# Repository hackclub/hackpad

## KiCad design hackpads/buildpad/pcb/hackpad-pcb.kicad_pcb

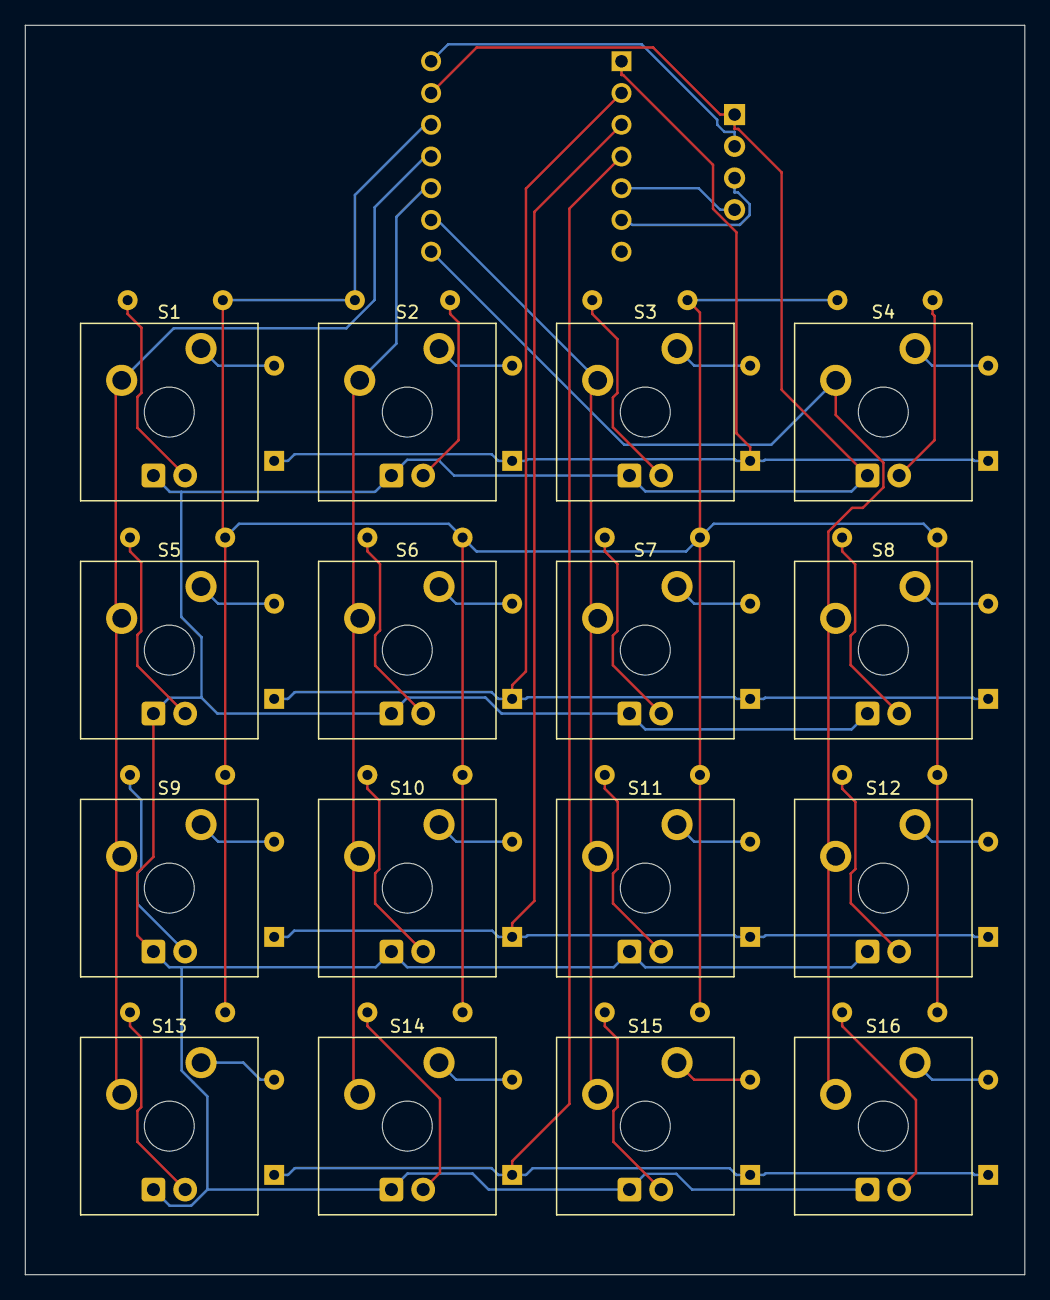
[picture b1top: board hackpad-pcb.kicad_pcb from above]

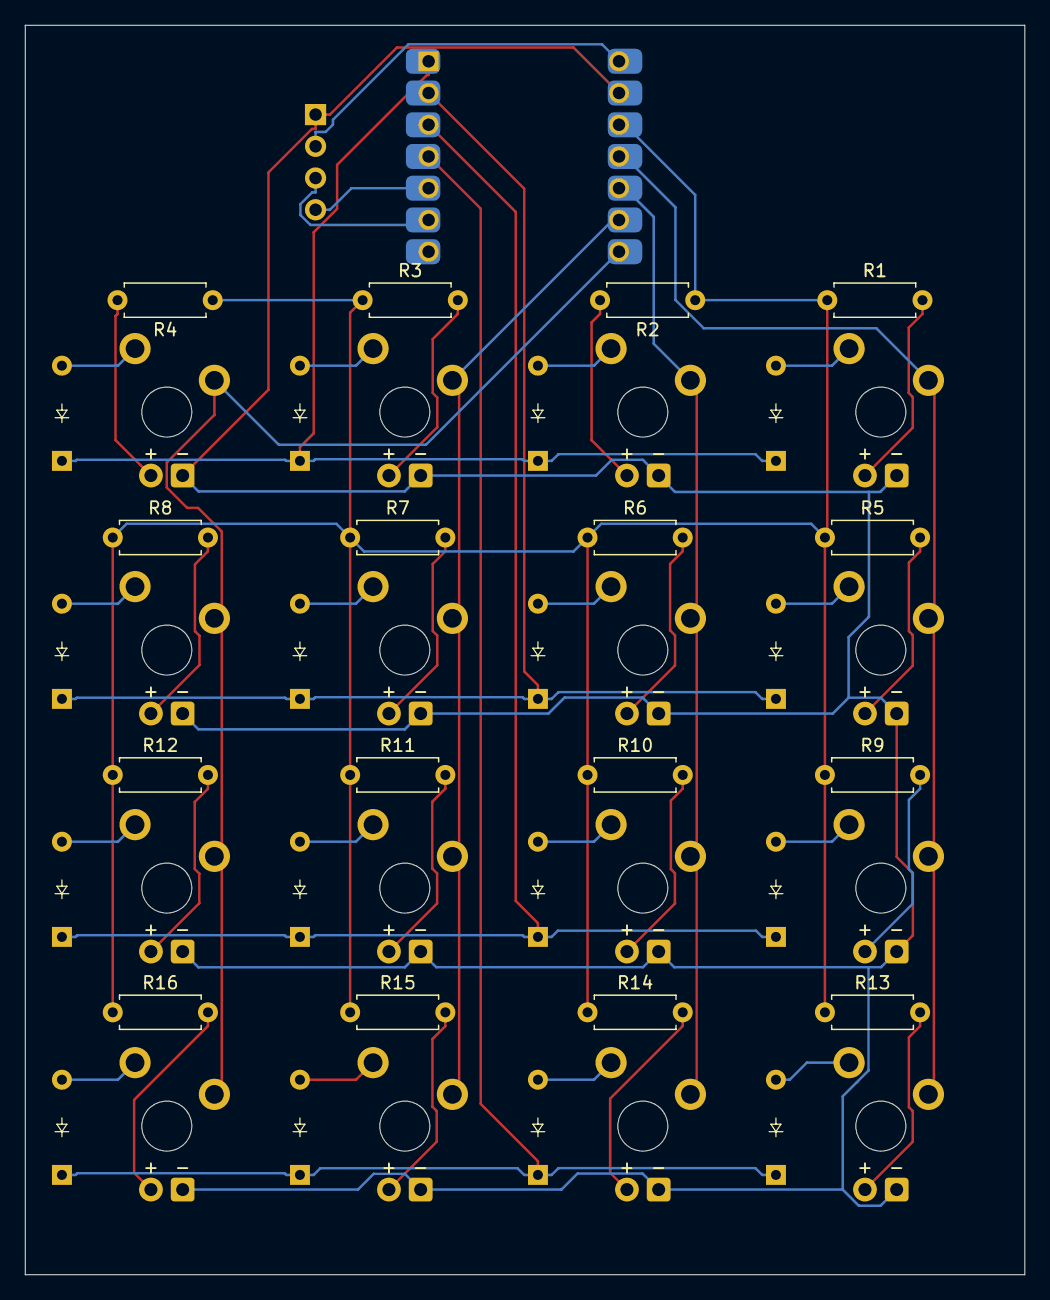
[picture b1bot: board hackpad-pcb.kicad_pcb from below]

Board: 2 copper layers, 80.0 x 100.0 mm, 66 parts (33 on the bottom side), 45 nets.

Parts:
D1, D2, D3, D4, D5, D6, D7, D8, D9, D10, D11, D12, D13, D14, D15, D16: Diode; Diode_DO-35
D17, D18, D19, D20, D21, D22, D23, D24, D25, D26, D27, D28, D29, D30, D31, D32: LED; LED_MX_3mm-ROT
J1: OLED_128x32
R1, R2, R3, R4, R5, R6, R7, R8, R9, R10, R11, R12, R13, R14, R15, R16: R; R_Axial_DIN0207_L6.3mm_D2.5mm_P7.62mm_Horizontal
S1, S2, S3, S4, S5, S6, S7, S8, S9, S10, S11, S12, S13, S14, S15, S16: Keyswitch; MX_Plate_1.00u
U1: MCU_Seeed_XIAO_RP2040; Seeed_XIAO_RP2040

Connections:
+3V3: R1.1, R2.1, R3.1, R4.1, R5.1, R6.1, R7.1, R8.1, R9.1, R10.1, R11.1, R12.1, R13.1, R14.1, R15.1, R16.1, U1.12 (3V3)
Column 0: S1.1, S5.1, S9.1, S13.1, U1.11 (PA6_A10_D10_MOSI)
Column 1: S2.1, S6.1, S10.1, S14.1, U1.10 (PA5_A9_D9_MISO)
Column 2: S3.1, S7.1, S11.1, S15.1, U1.9 (PA7_A8_D8_SCK)
Column 3: S4.1, S8.1, S12.1, S16.1, U1.8 (PB09_A7_D7_RX)
GND: D17.1 (K), D18.1 (K), D19.1 (K), D20.1 (K), D21.1 (K), D22.1 (K), D23.1 (K), D24.1 (K), D25.1 (K), D26.1 (K), D27.1 (K), D28.1 (K), D29.1 (K), D30.1 (K), D31.1 (K), D32.1 (K), J1.1 (GND), U1.13 (GND)
unnamed: D1.2 (A), S1.2
unnamed: D2.2 (A), S2.2
unnamed: D3.2 (A), S3.2
unnamed: D4.2 (A), S4.2
unnamed: D5.2 (A), S5.2
unnamed: D6.2 (A), S6.2
unnamed: D7.2 (A), S7.2
unnamed: D8.2 (A), S8.2
unnamed: D9.2 (A), S9.2
unnamed: D10.2 (A), S10.2
unnamed: D11.2 (A), S11.2
unnamed: D12.2 (A), S12.2
unnamed: D13.2 (A), S13.2
unnamed: D14.2 (A), S14.2
unnamed: D15.2 (A), S15.2
unnamed: D16.2 (A), S16.2
unnamed: D17.2 (A), R1.2
unnamed: D18.2 (A), R2.2
unnamed: D19.2 (A), R3.2
unnamed: D20.2 (A), R4.2
unnamed: D21.2 (A), R5.2
unnamed: D22.2 (A), R6.2
unnamed: D23.2 (A), R7.2
unnamed: D24.2 (A), R8.2
unnamed: D25.2 (A), R9.2
unnamed: D26.2 (A), R10.2
unnamed: D27.2 (A), R11.2
unnamed: D28.2 (A), R12.2
unnamed: D29.2 (A), R13.2
unnamed: D30.2 (A), R14.2
unnamed: D31.2 (A), R15.2
unnamed: D32.2 (A), R16.2
Row 0: D1.1 (K), D2.1 (K), D3.1 (K), D4.1 (K), U1.1 (PA02_A0_D0)
Row 1: D5.1 (K), D6.1 (K), D7.1 (K), D8.1 (K), U1.2 (PA4_A1_D1)
Row 2: D9.1 (K), D10.1 (K), D11.1 (K), D12.1 (K), U1.3 (PA10_A2_D2)
Row 3: D13.1 (K), D14.1 (K), D15.1 (K), D16.1 (K), U1.4 (PA11_A3_D3)
SCL: J1.3 (SCL), U1.6 (PA9_A5_D5_SCL)
SDA: J1.4 (SDA), U1.5 (PA8_A4_D4_SDA)
VCC: J1.2 (VCC), U1.14 (5V)

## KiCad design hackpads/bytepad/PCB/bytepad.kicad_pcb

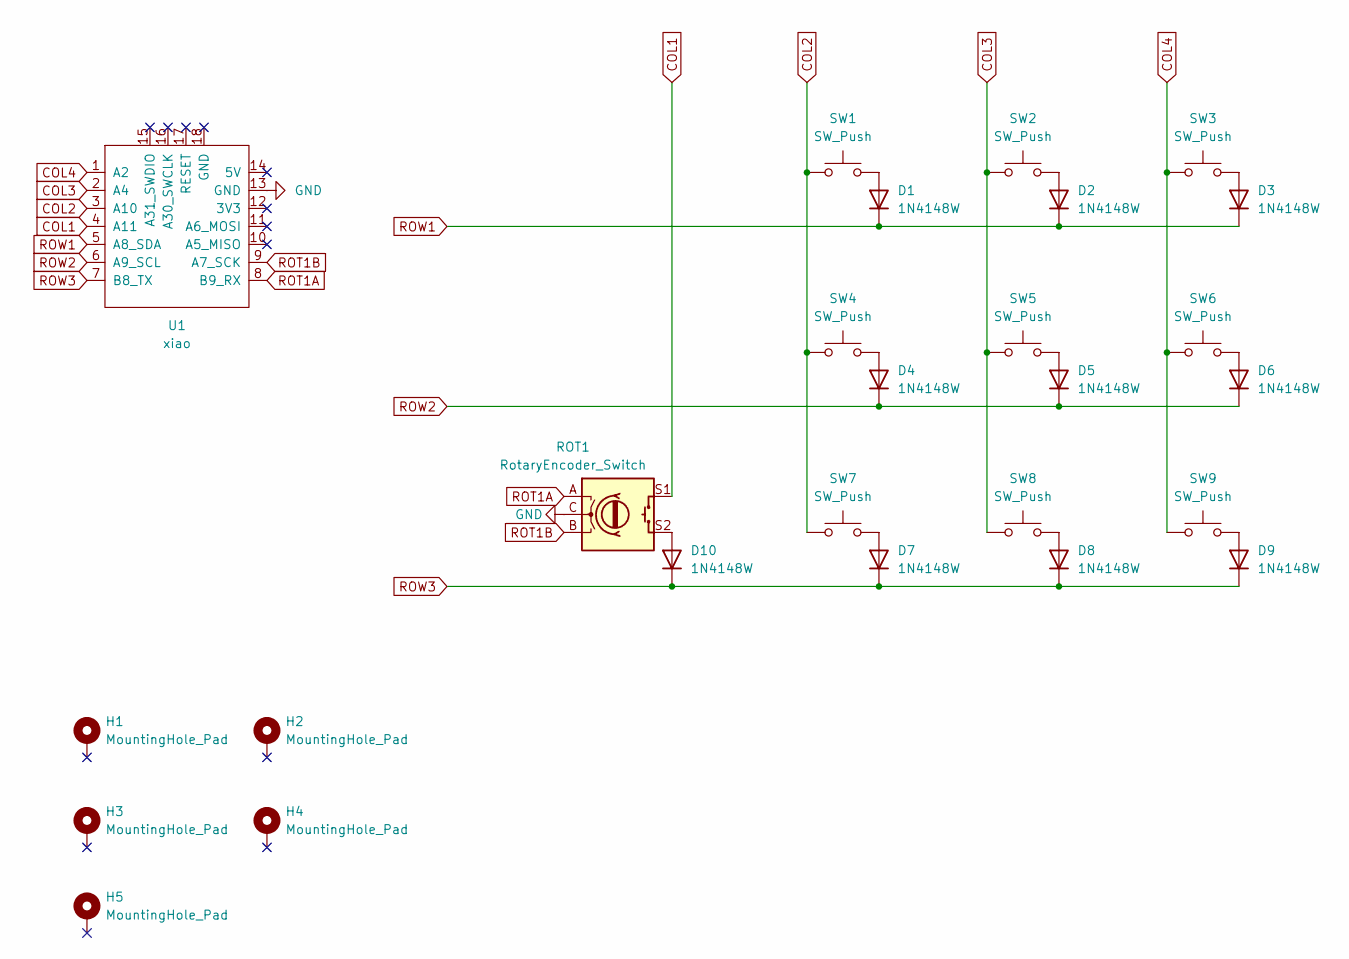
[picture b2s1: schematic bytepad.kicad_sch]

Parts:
D1, D2, D3, D4, D5, D6, D7, D8, D9, D10: 1N4148W; D_SOD-123
H1, H2, H3, H4, H5: MountingHole_Pad; MountingHole_2.2mm_M2_DIN965_Pad
ROT1: RotaryEncoder_Switch; RotaryEncoder_EC11
SW1, SW2, SW3, SW4, SW5, SW6, SW7, SW8, SW9: SW_Push; pg1350-H
U1: xiao; xiao-tht

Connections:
COL1: ROT1.S1, U1.4 (A11)
COL2: SW1.1, SW4.1, SW7.1, U1.3 (A10)
COL3: SW2.1, SW5.1, SW8.1, U1.2 (A4)
COL4: SW3.1, SW6.1, SW9.1, U1.1 (A2)
GND: ROT1.C, U1.13 (GND)
unnamed: D1.2 (A), SW1.2
unnamed: D2.2 (A), SW2.2
unnamed: D3.2 (A), SW3.2
unnamed: D4.2 (A), SW4.2
unnamed: D5.2 (A), SW5.2
unnamed: D6.2 (A), SW6.2
unnamed: D7.2 (A), SW7.2
unnamed: D8.2 (A), SW8.2
unnamed: D9.2 (A), SW9.2
unnamed: D10.2 (A), ROT1.S2
ROT1A: ROT1.A, U1.8 (B9_RX)
ROT1B: ROT1.B, U1.9 (A7_SCK)
ROW1: D1.1 (K), D2.1 (K), D3.1 (K), U1.5 (A8_SDA)
ROW2: D4.1 (K), D5.1 (K), D6.1 (K), U1.6 (A9_SCL)
ROW3: D7.1 (K), D8.1 (K), D9.1 (K), D10.1 (K), U1.7 (B8_TX)

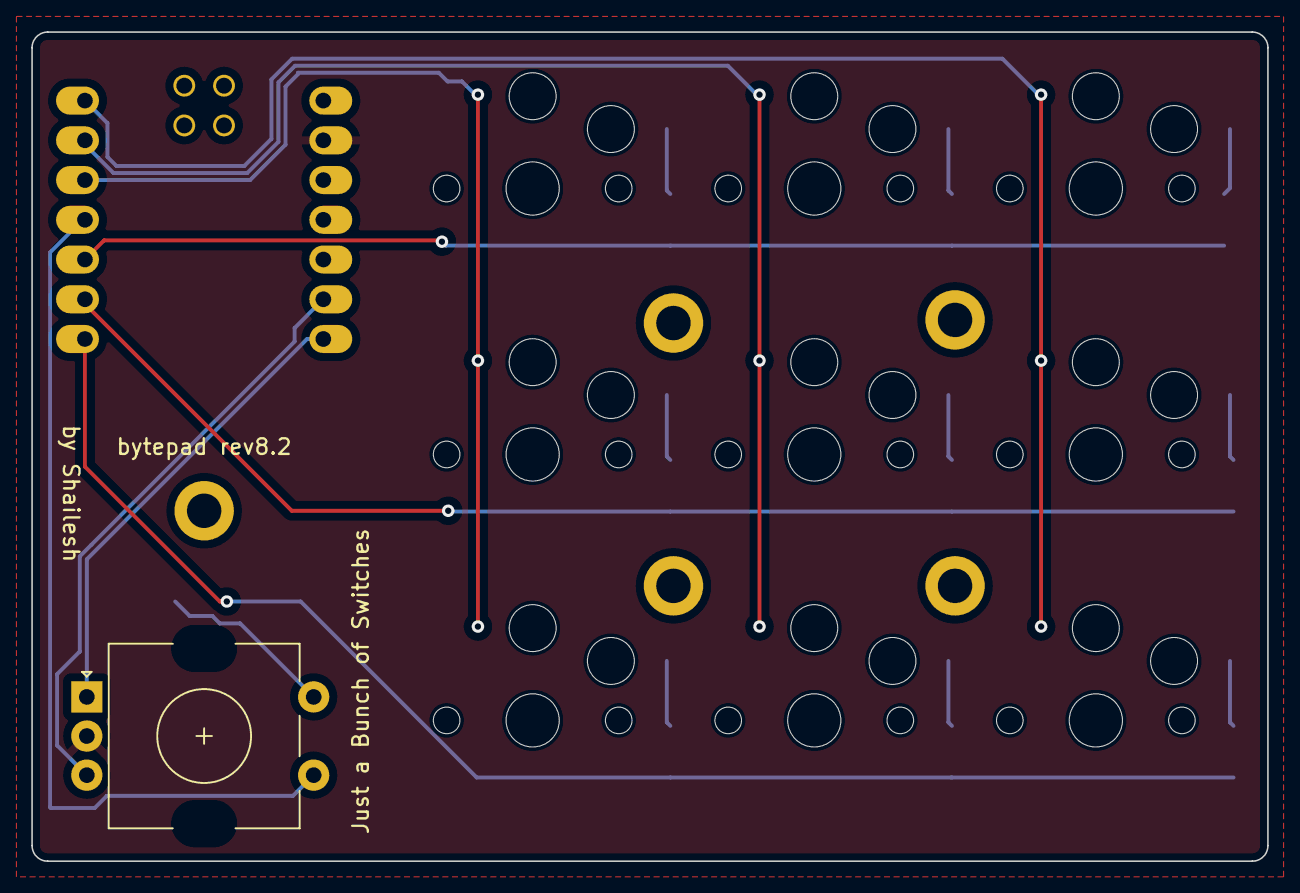
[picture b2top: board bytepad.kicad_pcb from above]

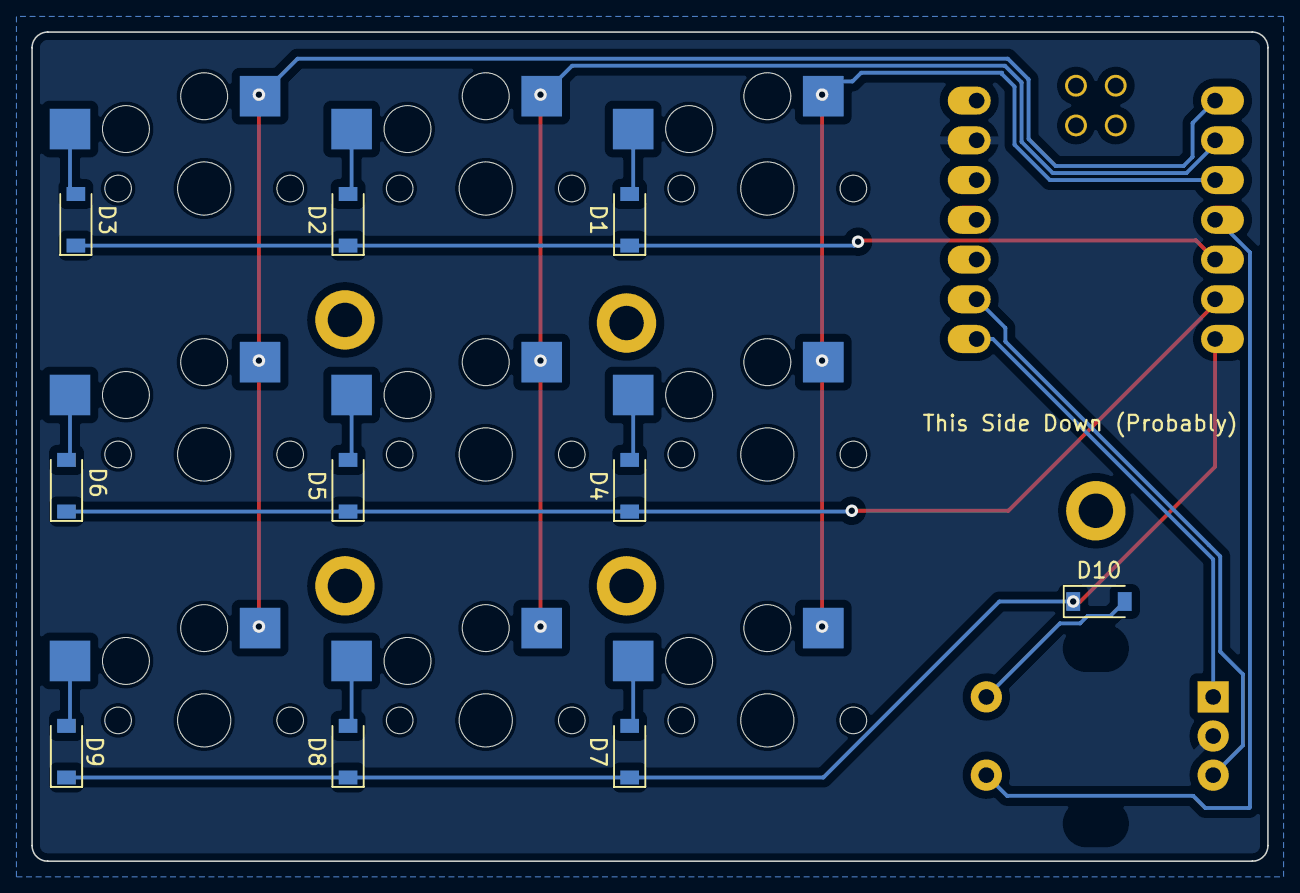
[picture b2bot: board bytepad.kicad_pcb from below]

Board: 2 copper layers, 79.0 x 53.0 mm, 26 parts (10 on the bottom side), 20 nets.

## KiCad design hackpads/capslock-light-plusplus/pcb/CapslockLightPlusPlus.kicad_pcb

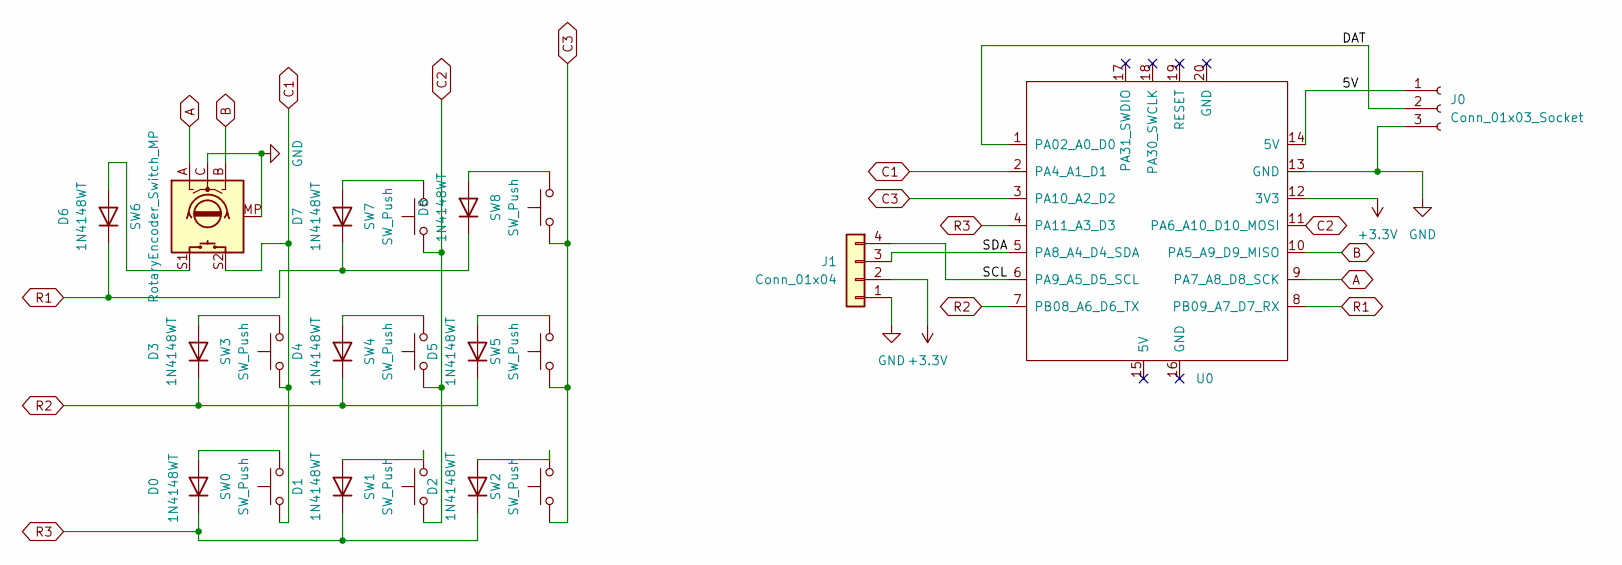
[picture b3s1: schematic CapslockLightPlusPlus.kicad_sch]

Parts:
D0, D1, D2, D3, D4, D5, D6, D7, D8: 1N4148WT; DIODE-1N4148
J0: Conn_01x03_Socket; SolderJumper-3_P1.3mm_Open_Pad1.0x1.5mm
J1: Conn_01x04; SSD1306-0.91-OLED-4pin-128x32
SW0, SW1, SW2, SW3, SW4, SW5, SW7, SW8: SW_Push; SW_Cherry_MX_1.00u_PCB
SW6: RotaryEncoder_Switch_MP; RotaryEncoder_Alps_EC12E-Switch_Vertical_H20mm
U0: Seeed Studio XIAO SAMD21; XIAO-Generic-Hybrid-14P-2.54-21X17.8MM

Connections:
+3.3V: J1.2 (Pin_3), U0.12 (3V3)
/5V: J0.1, U0.14 (5V)
/DAT: J0.2, U0.1 (PA02_A0_D0)
/SCL: J1.4 (Pin_1), U0.6 (PA9_A5_D5_SCL)
/SDA: J1.3 (Pin_2), U0.5 (PA8_A4_D4_SDA)
A: SW6.A, U0.9 (PA7_A8_D8_SCK)
B: SW6.B, U0.10 (PA5_A9_D9_MISO)
C1: SW0.1, SW3.1, SW6.S2, U0.2 (PA4_A1_D1)
C2: SW1.1, SW4.1, SW7.1, U0.11 (PA6_A10_D10_MOSI)
C3: SW2.1, SW5.1, SW8.1, U0.3 (PA10_A2_D2)
GND: J0.3, J1.1 (Pin_4), SW6.C, SW6.MP, U0.13 (GND)
unnamed: D0.2 (A), SW0.2
unnamed: D1.2 (A), SW1.2
unnamed: D2.2 (A), SW2.2
unnamed: D3.2 (A), SW3.2
unnamed: D4.2 (A), SW4.2
unnamed: D5.2 (A), SW5.2
unnamed: D6.2 (A), SW6.S1
unnamed: D7.2 (A), SW7.2
unnamed: D8.2 (A), SW8.2
R1: D6.1 (K), D7.1 (K), D8.1 (K), U0.8 (PB09_A7_D7_RX)
R2: D3.1 (K), D4.1 (K), D5.1 (K), U0.7 (PB08_A6_D6_TX)
R3: D0.1 (K), D1.1 (K), D2.1 (K), U0.4 (PA11_A3_D3)

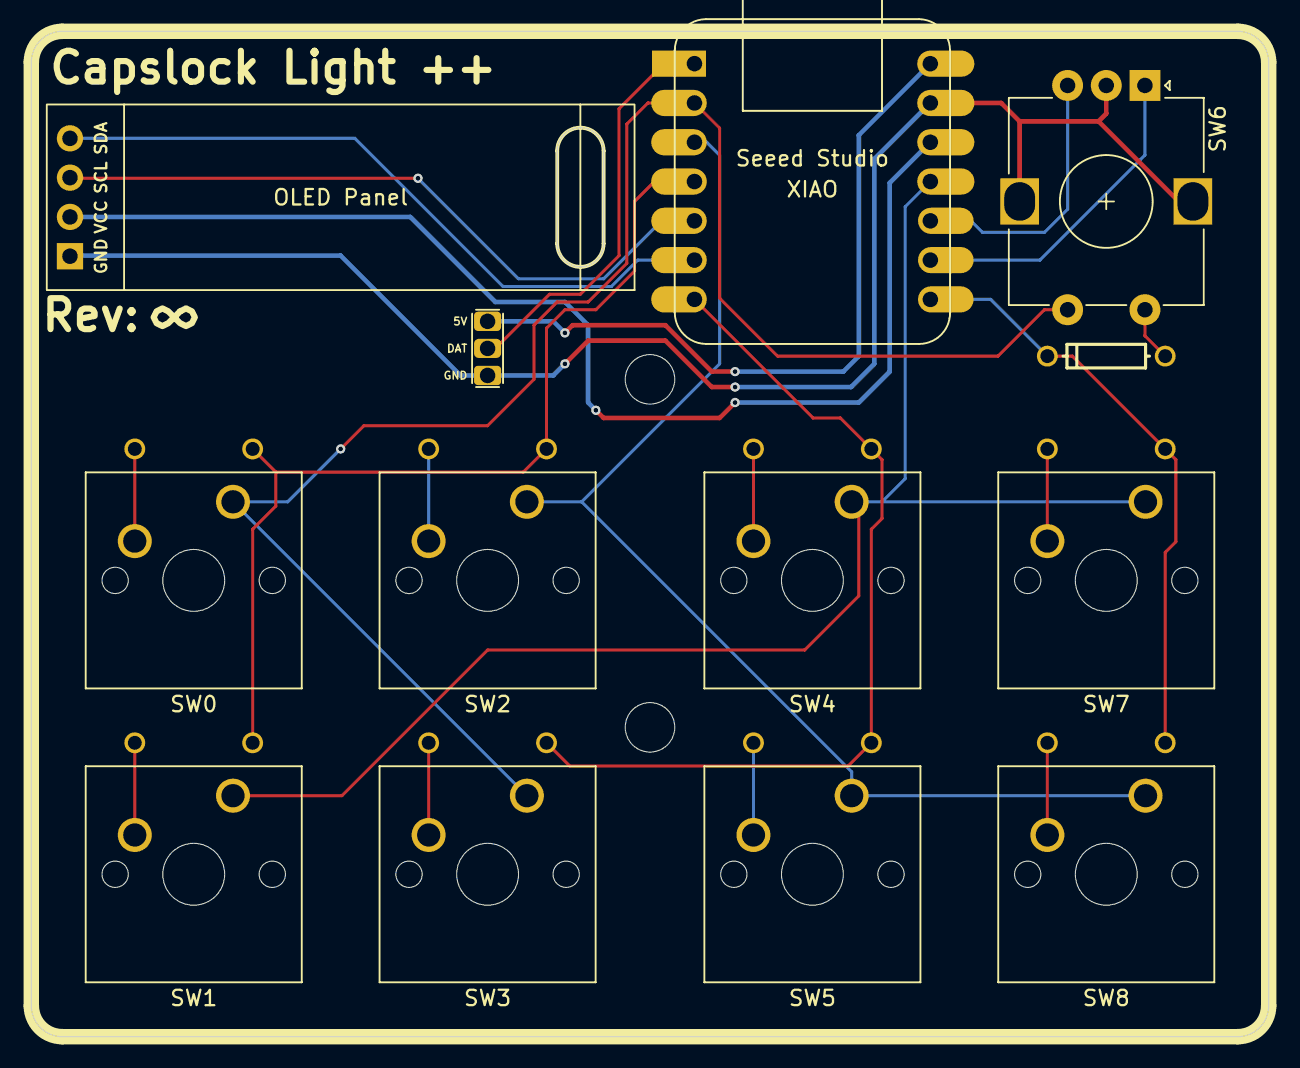
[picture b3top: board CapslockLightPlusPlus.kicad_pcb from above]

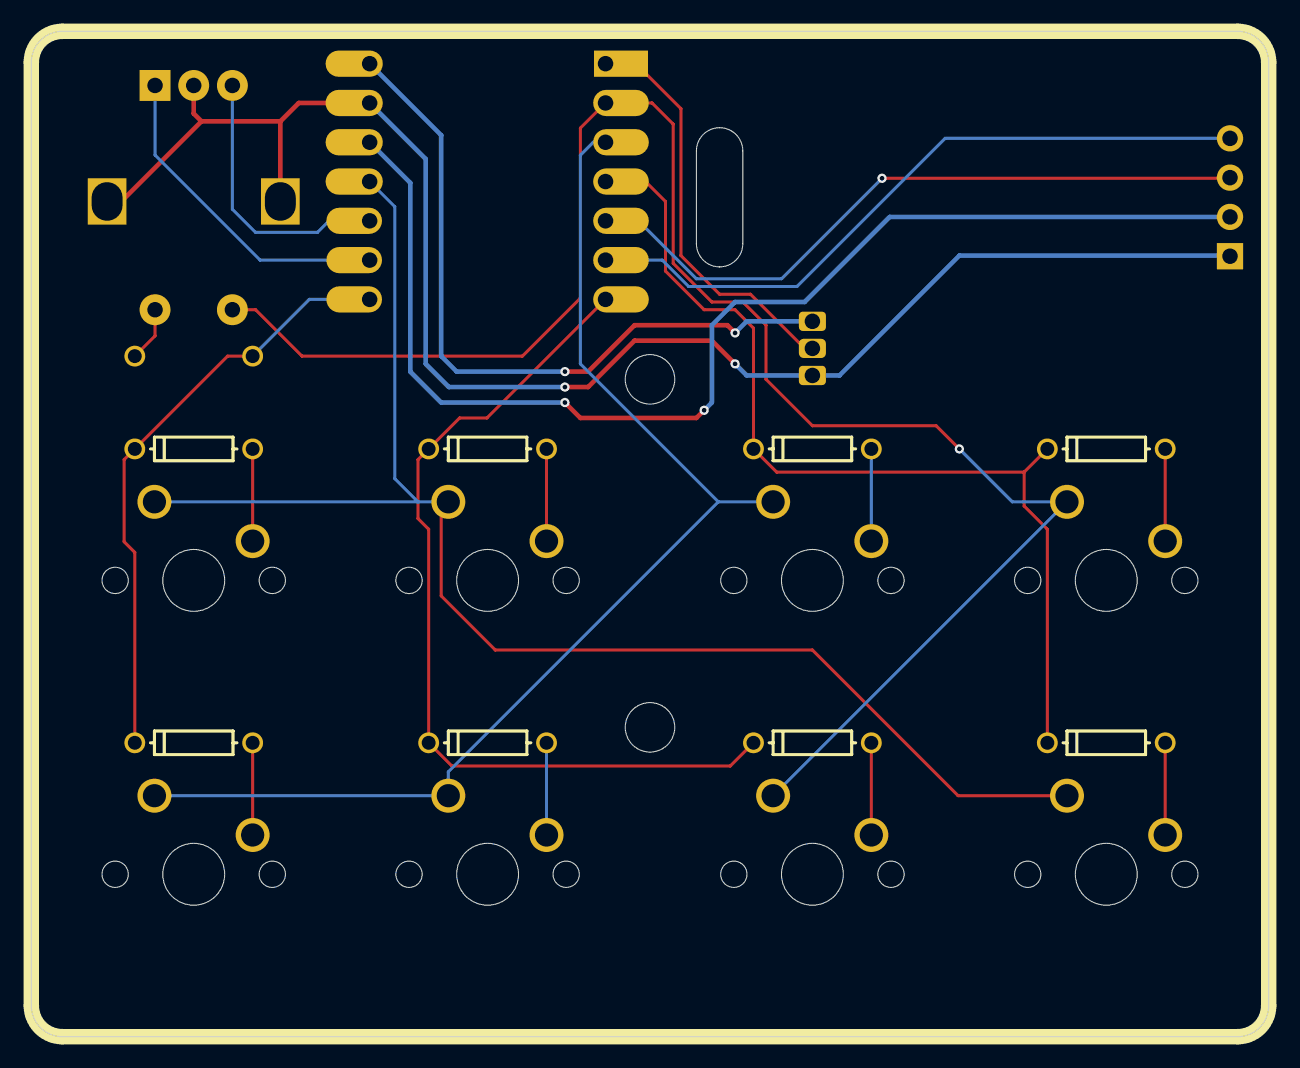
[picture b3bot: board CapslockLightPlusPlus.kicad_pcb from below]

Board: 2 copper layers, 80.0 x 65.0 mm, 21 parts (8 on the bottom side), 23 nets.

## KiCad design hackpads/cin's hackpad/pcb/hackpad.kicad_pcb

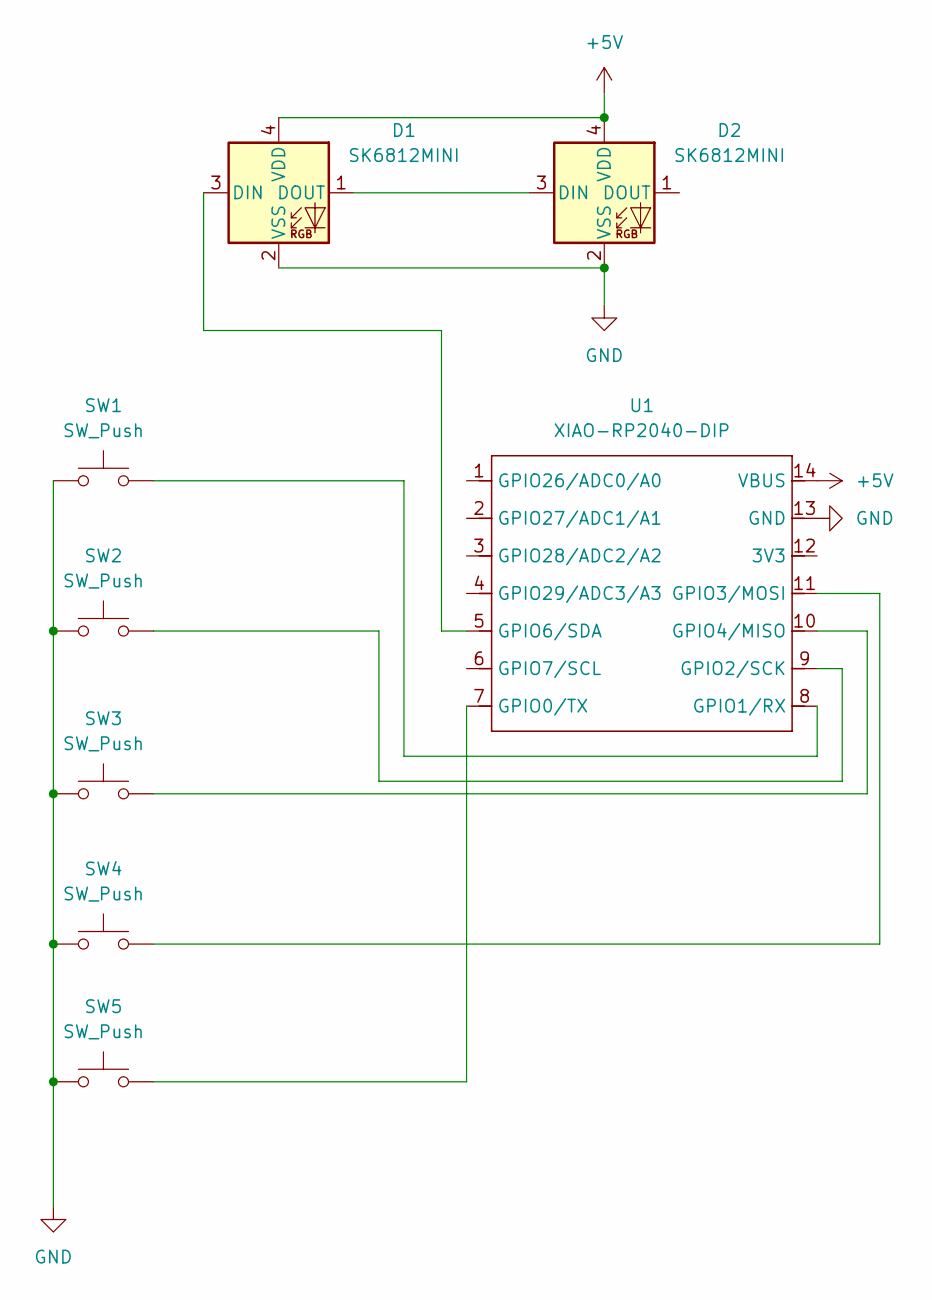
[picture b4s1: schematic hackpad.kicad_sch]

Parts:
D1, D2: SK6812MINI; LED_SK6812MINI_PLCC4_3.5x3.5mm_P1.75mm
SW1, SW2, SW3, SW4, SW5: SW_Push; SW_Cherry_MX_1.00u_PCB
U1: XIAO-RP2040-DIP

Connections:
+5V: D1.4 (VDD), D2.4 (VDD), U1.14 (VBUS)
GND: D1.2 (VSS), D2.2 (VSS), SW1.1, SW2.1, SW3.1, SW4.1, SW5.1, U1.13 (GND)
unnamed: D1.3 (DIN), U1.5 (GPIO6/SDA)
unnamed: D1.1 (DOUT), D2.3 (DIN)
unnamed: SW5.2, U1.7 (GPIO0/TX)
unnamed: SW1.2, U1.8 (GPIO1/RX)
unnamed: SW2.2, U1.9 (GPIO2/SCK)
unnamed: SW4.2, U1.11 (GPIO3/MOSI)
unnamed: SW3.2, U1.10 (GPIO4/MISO)

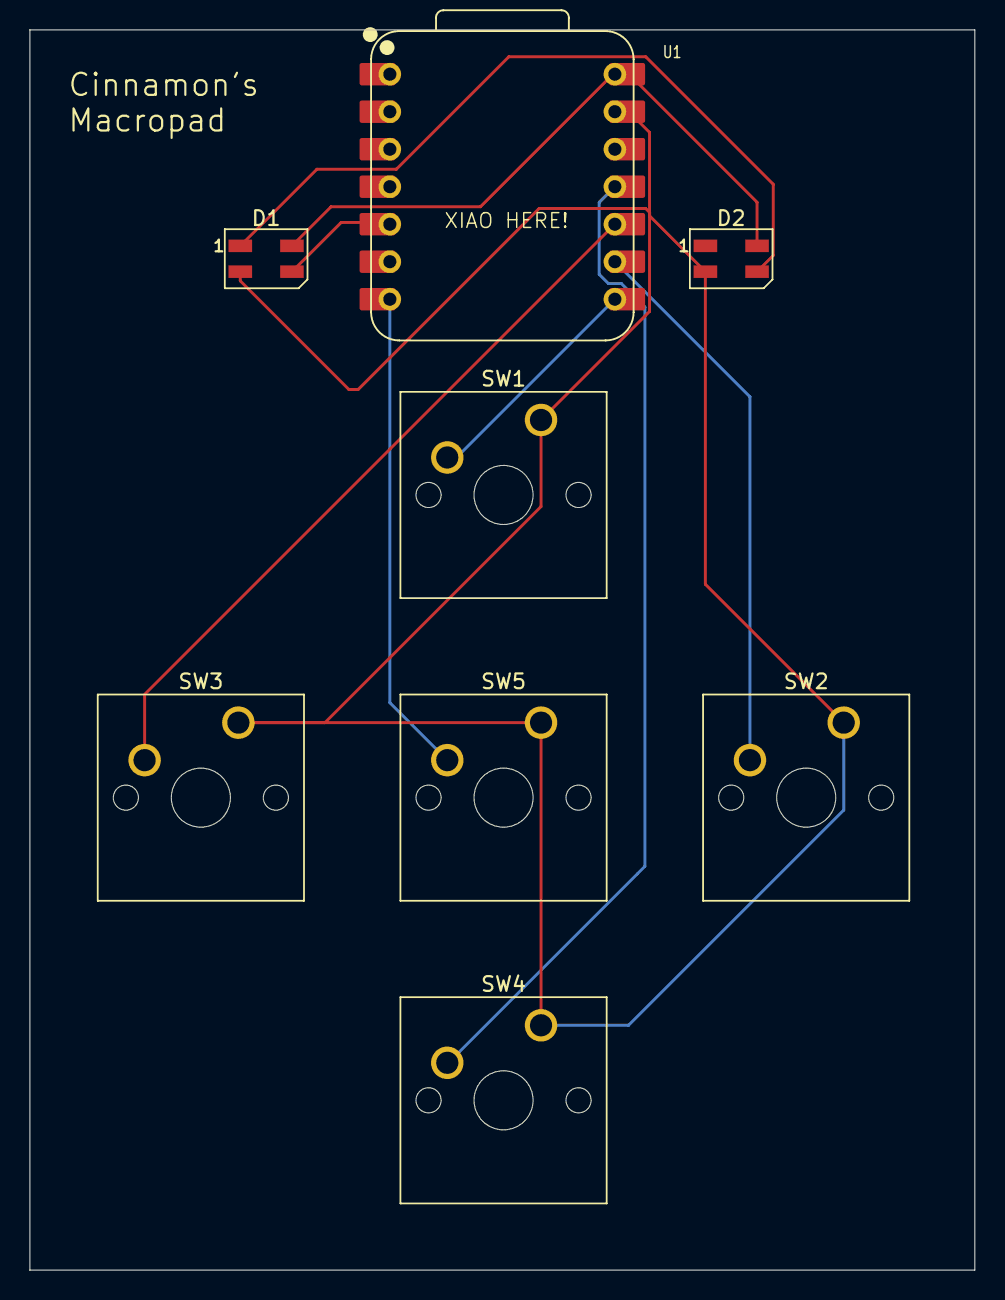
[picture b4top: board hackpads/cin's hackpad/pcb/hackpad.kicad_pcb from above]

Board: 2 copper layers, 64.0 x 84.0 mm, 8 parts (0 on the bottom side), 9 nets.

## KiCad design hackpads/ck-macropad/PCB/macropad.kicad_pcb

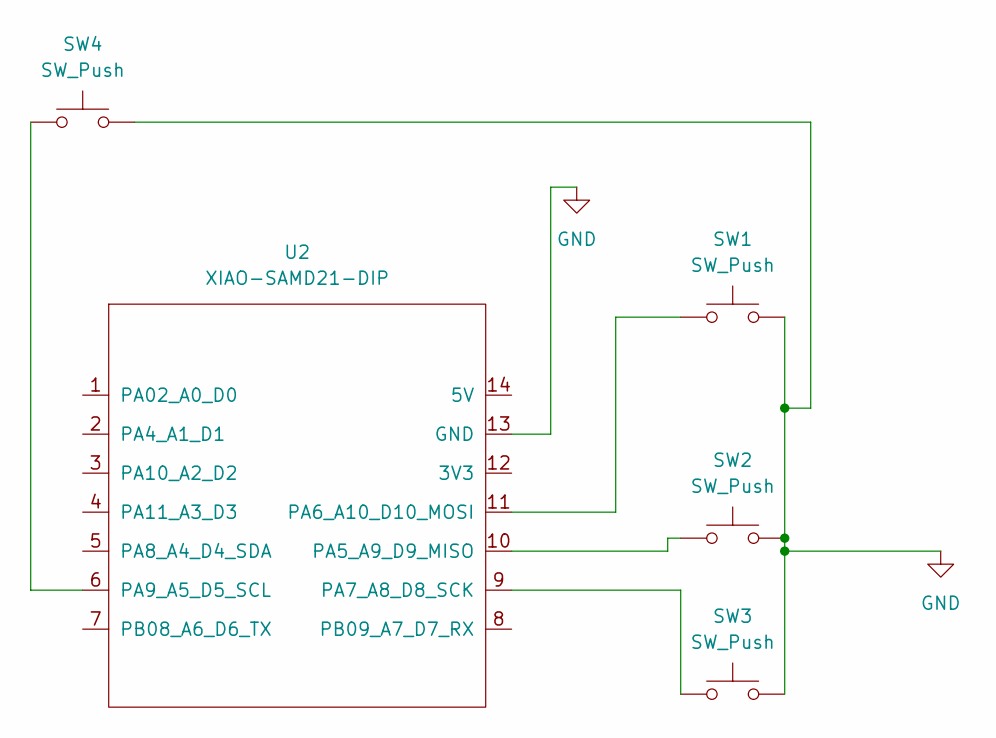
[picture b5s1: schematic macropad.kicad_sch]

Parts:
SW1, SW2, SW3, SW4: SW_Push; SW_Cherry_MX_1.00u_PCB
U2: XIAO-SAMD21-DIP; XIAO-nRF52840-DIP

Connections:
GND: SW1.2, SW2.2, SW3.2, SW4.2, U2.13 (GND)
unnamed: SW2.1, U2.10 (PA5_A9_D9_MISO)
unnamed: SW1.1, U2.11 (PA6_A10_D10_MOSI)
unnamed: SW3.1, U2.9 (PA7_A8_D8_SCK)
unnamed: SW4.1, U2.6 (PA9_A5_D5_SCL)

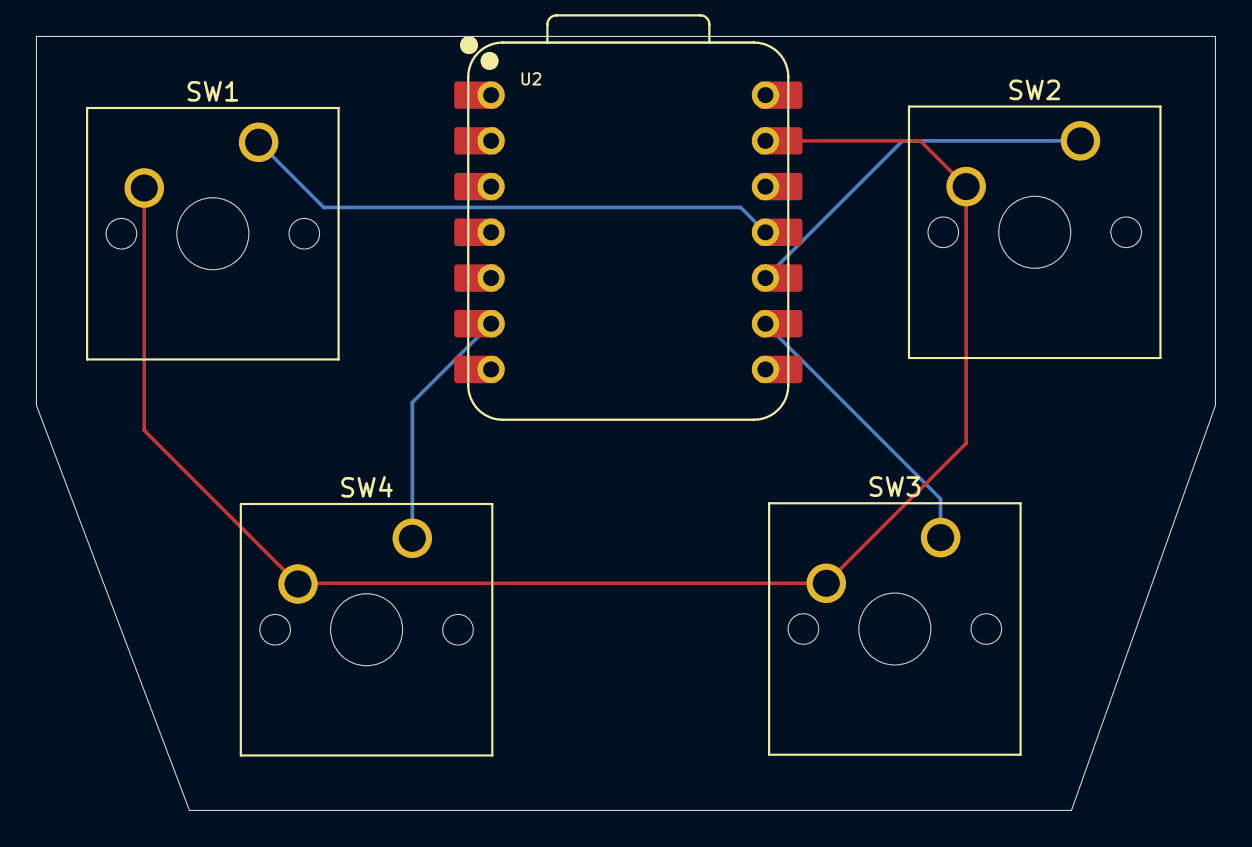
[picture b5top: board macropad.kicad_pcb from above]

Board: 2 copper layers, 65.5 x 43.0 mm, 5 parts (0 on the bottom side), 5 nets.

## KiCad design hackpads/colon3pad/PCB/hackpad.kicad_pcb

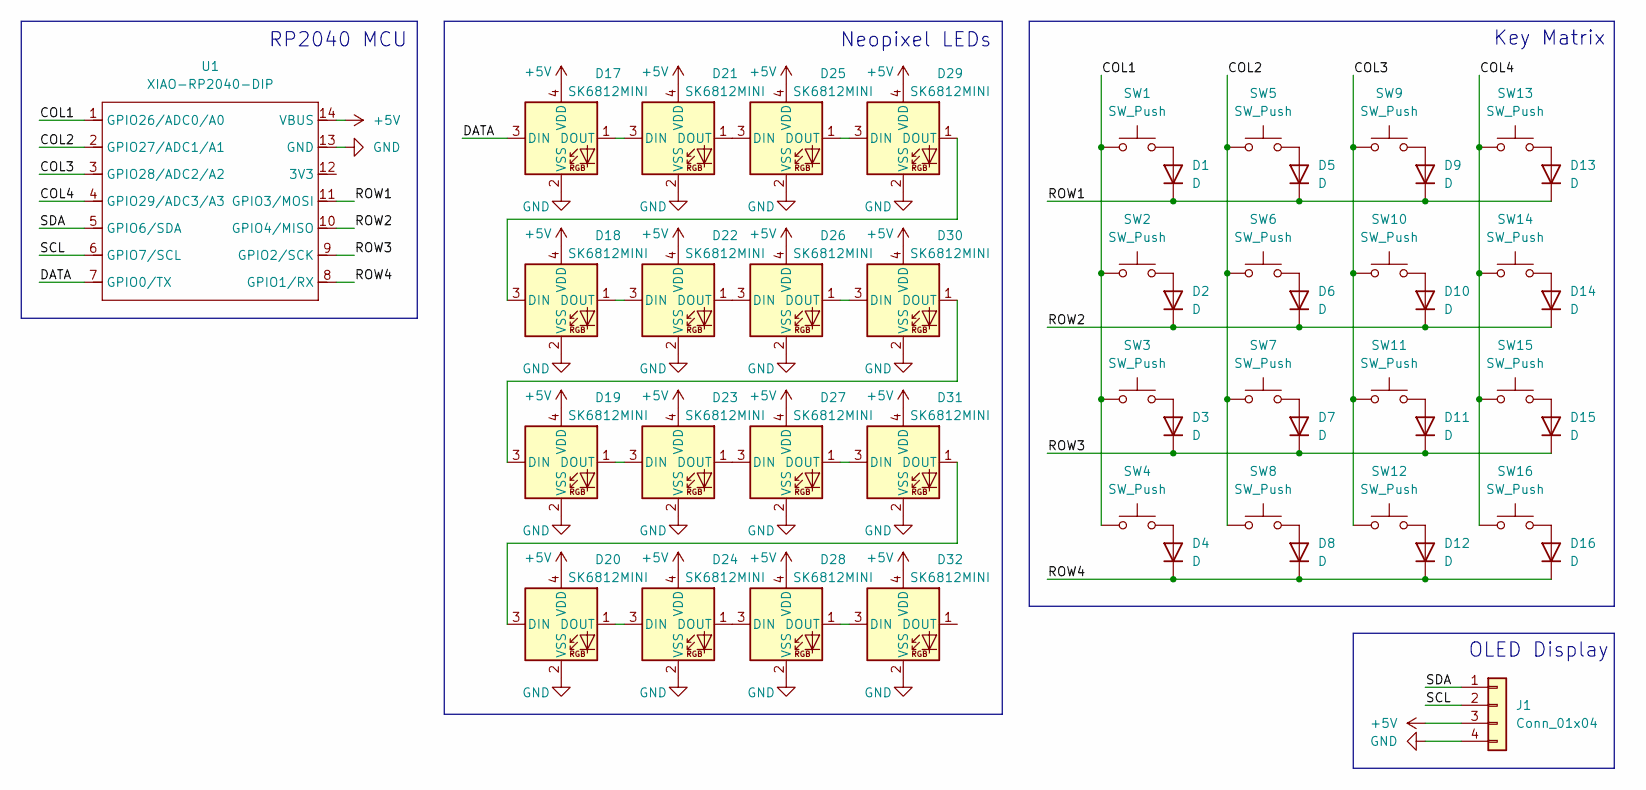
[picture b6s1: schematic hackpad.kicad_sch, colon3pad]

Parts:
D1, D2, D3, D4, D5, D6, D7, D8, D9, D10, D11, D12, D13, D14, D15, D16: D; D_DO-35_SOD27_P7.62mm_Horizontal
D17, D18, D19, D20, D21, D22, D23, D24, D25, D26, D27, D28, D29, D30, D31, D32: SK6812MINI; SK6812-MINI-E
J1: Conn_01x04; SSD1306-0.91-OLED-4pin-128x32
SW1, SW2, SW3, SW4, SW5, SW6, SW7, SW8, SW9, SW10, SW11, SW12, SW13, SW14, SW15, SW16: SW_Push; SW_Kailh_Choc_V2_1.00u
U1: XIAO-RP2040-DIP

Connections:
+5V: D17.4 (VDD), D18.4 (VDD), D19.4 (VDD), D20.4 (VDD), D21.4 (VDD), D22.4 (VDD), D23.4 (VDD), D24.4 (VDD), D25.4 (VDD), D26.4 (VDD), D27.4 (VDD), D28.4 (VDD), D29.4 (VDD), D30.4 (VDD), D31.4 (VDD), D32.4 (VDD), J1.3, U1.14 (VBUS)
/COL1: SW1.1, SW2.1, SW3.1, SW4.1, U1.1 (GPIO26/ADC0/A0)
/COL2: SW5.1, SW6.1, SW7.1, SW8.1, U1.2 (GPIO27/ADC1/A1)
/COL3: SW9.1, SW10.1, SW11.1, SW12.1, U1.3 (GPIO28/ADC2/A2)
/COL4: SW13.1, SW14.1, SW15.1, SW16.1, U1.4 (GPIO29/ADC3/A3)
/DATA: D17.3 (DIN), U1.7 (GPIO0/TX)
/ROW1: D1.1 (K), D5.1 (K), D9.1 (K), D13.1 (K), U1.11 (GPIO3/MOSI)
/ROW2: D2.1 (K), D6.1 (K), D10.1 (K), D14.1 (K), U1.10 (GPIO4/MISO)
/ROW3: D3.1 (K), D7.1 (K), D11.1 (K), D15.1 (K), U1.9 (GPIO2/SCK)
/ROW4: D4.1 (K), D8.1 (K), D12.1 (K), D16.1 (K), U1.8 (GPIO1/RX)
/SCL: J1.2, U1.6 (GPIO7/SCL)
/SDA: J1.1, U1.5 (GPIO6/SDA)
GND: D17.2 (VSS), D18.2 (VSS), D19.2 (VSS), D20.2 (VSS), D21.2 (VSS), D22.2 (VSS), D23.2 (VSS), D24.2 (VSS), D25.2 (VSS), D26.2 (VSS), D27.2 (VSS), D28.2 (VSS), D29.2 (VSS), D30.2 (VSS), D31.2 (VSS), D32.2 (VSS), J1.4, U1.13 (GND)
unnamed: D1.2 (A), SW1.2
unnamed: D2.2 (A), SW2.2
unnamed: D3.2 (A), SW3.2
unnamed: D4.2 (A), SW4.2
unnamed: D5.2 (A), SW5.2
unnamed: D6.2 (A), SW6.2
unnamed: D7.2 (A), SW7.2
unnamed: D8.2 (A), SW8.2
unnamed: D9.2 (A), SW9.2
unnamed: D10.2 (A), SW10.2
unnamed: D11.2 (A), SW11.2
unnamed: D12.2 (A), SW12.2
unnamed: D13.2 (A), SW13.2
unnamed: D14.2 (A), SW14.2
unnamed: D15.2 (A), SW15.2
unnamed: D16.2 (A), SW16.2
unnamed: D17.1 (DOUT), D21.3 (DIN)
unnamed: D18.3 (DIN), D29.1 (DOUT)
unnamed: D18.1 (DOUT), D22.3 (DIN)
unnamed: D19.3 (DIN), D30.1 (DOUT)
unnamed: D19.1 (DOUT), D23.3 (DIN)
unnamed: D20.3 (DIN), D31.1 (DOUT)
unnamed: D20.1 (DOUT), D24.3 (DIN)
unnamed: D21.1 (DOUT), D25.3 (DIN)
unnamed: D22.1 (DOUT), D26.3 (DIN)
unnamed: D23.1 (DOUT), D27.3 (DIN)
unnamed: D24.1 (DOUT), D28.3 (DIN)
unnamed: D25.1 (DOUT), D29.3 (DIN)
unnamed: D26.1 (DOUT), D30.3 (DIN)
unnamed: D27.1 (DOUT), D31.3 (DIN)
unnamed: D28.1 (DOUT), D32.3 (DIN)

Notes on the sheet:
OLED Display
Neopixel LEDs
Key Matrix
RP2040 MCU
